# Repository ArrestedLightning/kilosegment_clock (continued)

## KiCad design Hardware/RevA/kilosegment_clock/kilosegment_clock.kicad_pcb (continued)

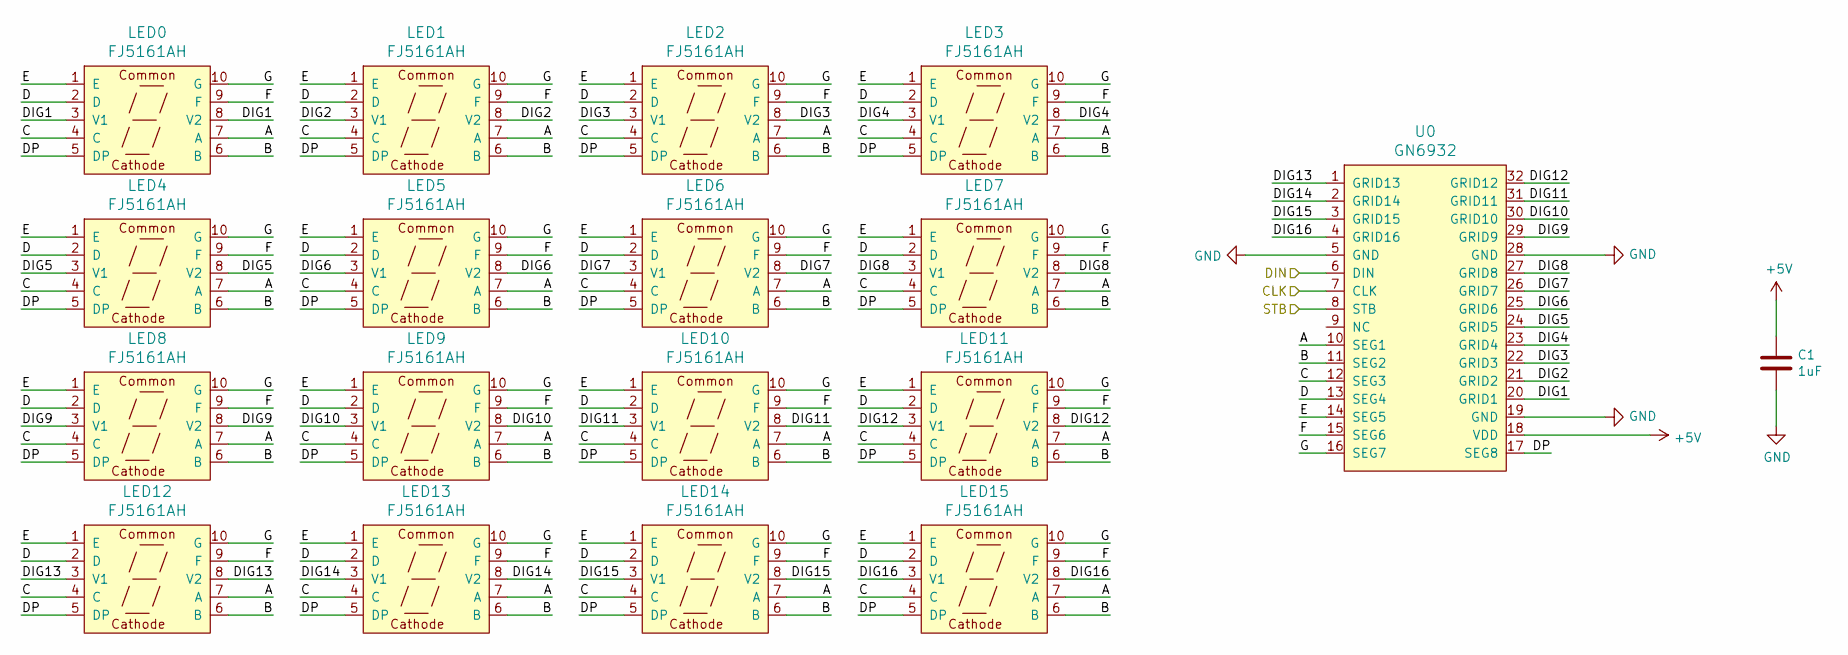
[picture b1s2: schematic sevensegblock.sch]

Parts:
C1: 1uF; C_0805_2012Metric_Pad1.18x1.45mm_HandSolder; Digikey 1276-1026-1-ND
LED0: FJ5161AH; LED-SEG-TH_FJ5161BH; LCSC Part C8092, C141367
LED1, LED2, LED3, LED4, LED5, LED6, LED7, LED8, LED9, LED10, LED11, LED12, LED13, LED14, LED15: FJ5161AH; LED-SEG-TH_FJ5161BH; LCSC Part C8092
U0: GN6932; SOP-32_L21.0-W7.5-P1.27-LS10.4-BL; LCSC Part C265476

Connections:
+5V: C1.1, U0.18 (VDD); also elsewhere on the board
/CLK: U0.7 (CLK); also elsewhere on the board
/CS0: U0.8 (STB); also elsewhere on the board
/DIN: U0.6 (DIN); also elsewhere on the board
/Sheet65B35949/A: LED0.7 (A), LED1.7 (A), LED2.7 (A), LED3.7 (A), LED4.7 (A), LED5.7 (A), LED6.7 (A), LED7.7 (A), LED8.7 (A), LED9.7 (A), LED10.7 (A), LED11.7 (A), LED12.7 (A), LED13.7 (A), LED14.7 (A), LED15.7 (A), U0.10 (SEG1)
/Sheet65B35949/B: LED0.6 (B), LED1.6 (B), LED2.6 (B), LED3.6 (B), LED4.6 (B), LED5.6 (B), LED6.6 (B), LED7.6 (B), LED8.6 (B), LED9.6 (B), LED10.6 (B), LED11.6 (B), LED12.6 (B), LED13.6 (B), LED14.6 (B), LED15.6 (B), U0.11 (SEG2)
/Sheet65B35949/C: LED0.4 (C), LED1.4 (C), LED2.4 (C), LED3.4 (C), LED4.4 (C), LED5.4 (C), LED6.4 (C), LED7.4 (C), LED8.4 (C), LED9.4 (C), LED10.4 (C), LED11.4 (C), LED12.4 (C), LED13.4 (C), LED14.4 (C), LED15.4 (C), U0.12 (SEG3)
/Sheet65B35949/D: LED0.2 (D), LED1.2 (D), LED2.2 (D), LED3.2 (D), LED4.2 (D), LED5.2 (D), LED6.2 (D), LED7.2 (D), LED8.2 (D), LED9.2 (D), LED10.2 (D), LED11.2 (D), LED12.2 (D), LED13.2 (D), LED14.2 (D), LED15.2 (D), U0.13 (SEG4)
/Sheet65B35949/DIG1: LED0.3 (V1), LED0.8 (V2), U0.20 (GRID1)
/Sheet65B35949/DIG2: LED1.3 (V1), LED1.8 (V2), U0.21 (GRID2)
/Sheet65B35949/DIG3: LED2.3 (V1), LED2.8 (V2), U0.22 (GRID3)
/Sheet65B35949/DIG4: LED3.3 (V1), LED3.8 (V2), U0.23 (GRID4)
/Sheet65B35949/DIG5: LED4.3 (V1), LED4.8 (V2), U0.24 (GRID5)
/Sheet65B35949/DIG6: LED5.3 (V1), LED5.8 (V2), U0.25 (GRID6)
/Sheet65B35949/DIG7: LED6.3 (V1), LED6.8 (V2), U0.26 (GRID7)
/Sheet65B35949/DIG8: LED7.3 (V1), LED7.8 (V2), U0.27 (GRID8)
/Sheet65B35949/DIG9: LED8.3 (V1), LED8.8 (V2), U0.29 (GRID9)
/Sheet65B35949/DIG10: LED9.3 (V1), LED9.8 (V2), U0.30 (GRID10)
/Sheet65B35949/DIG11: LED10.3 (V1), LED10.8 (V2), U0.31 (GRID11)
/Sheet65B35949/DIG12: LED11.3 (V1), LED11.8 (V2), U0.32 (GRID12)
/Sheet65B35949/DIG13: LED12.3 (V1), LED12.8 (V2), U0.1 (GRID13)
/Sheet65B35949/DIG14: LED13.3 (V1), LED13.8 (V2), U0.2 (GRID14)
/Sheet65B35949/DIG15: LED14.3 (V1), LED14.8 (V2), U0.3 (GRID15)
/Sheet65B35949/DIG16: LED15.3 (V1), LED15.8 (V2), U0.4 (GRID16)
/Sheet65B35949/DP: LED0.5 (DP), LED1.5 (DP), LED2.5 (DP), LED3.5 (DP), LED4.5 (DP), LED5.5 (DP), LED6.5 (DP), LED7.5 (DP), LED8.5 (DP), LED9.5 (DP), LED10.5 (DP), LED11.5 (DP), LED12.5 (DP), LED13.5 (DP), LED14.5 (DP), LED15.5 (DP), U0.17 (SEG8)
/Sheet65B35949/E: LED0.1 (E), LED1.1 (E), LED2.1 (E), LED3.1 (E), LED4.1 (E), LED5.1 (E), LED6.1 (E), LED7.1 (E), LED8.1 (E), LED9.1 (E), LED10.1 (E), LED11.1 (E), LED12.1 (E), LED13.1 (E), LED14.1 (E), LED15.1 (E), U0.14 (SEG5)
/Sheet65B35949/F: LED0.9 (F), LED1.9 (F), LED2.9 (F), LED3.9 (F), LED4.9 (F), LED5.9 (F), LED6.9 (F), LED7.9 (F), LED8.9 (F), LED9.9 (F), LED10.9 (F), LED11.9 (F), LED12.9 (F), LED13.9 (F), LED14.9 (F), LED15.9 (F), U0.15 (SEG6)
/Sheet65B35949/G: LED0.10 (G), LED1.10 (G), LED2.10 (G), LED3.10 (G), LED4.10 (G), LED5.10 (G), LED6.10 (G), LED7.10 (G), LED8.10 (G), LED9.10 (G), LED10.10 (G), LED11.10 (G), LED12.10 (G), LED13.10 (G), LED14.10 (G), LED15.10 (G), U0.16 (SEG7)
GND: C1.2, U0.5 (GND), U0.19 (GND), U0.28 (GND); also elsewhere on the board

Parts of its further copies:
C2, C3, C4, C5, C6, C7, C8, C9: 1uF; C_0805_2012Metric_Pad1.18x1.45mm_HandSolder; Digikey 1276-1026-1-ND
LED16, LED32, LED48, LED64, LED80, LED96, LED112, LED128: FJ5161AH; LED-SEG-TH_FJ5161BH; LCSC Part C8092, C141367
LED17, LED18, LED19, LED20, LED21, LED22, LED23, LED24, LED25, LED26, LED27, LED28, LED29, LED30, LED31, LED33, LED34, LED35, LED36, LED37, LED38, LED39, LED40, LED41, LED42, LED43, LED44, LED45, LED46, LED47, LED49, LED50, LED51, LED52, LED53, LED54, LED55, LED56, LED57, LED58, LED59, LED60, LED61, LED62, LED63, LED65, LED66, LED67, LED68, LED69, LED70, LED71, LED72, LED73, LED74, LED75, LED76, LED77, LED78, LED79, LED81, LED82, LED83, LED84, LED85, LED86, LED87, LED88, LED89, LED90, LED91, LED92, LED93, LED94, LED95, LED97, LED98, LED99, LED100, LED101, LED102, LED103, LED104, LED105, LED106, LED107, LED108, LED109, LED110, LED111, LED113, LED114, LED115, LED116, LED117, LED118, LED119, LED120, LED121, LED122, LED123, LED124, LED125, LED126, LED127, LED129, LED130, LED131, LED132, LED133, LED134, LED135, LED136, LED137, LED138, LED139, LED140, LED141, LED142, LED143: FJ5161AH; LED-SEG-TH_FJ5161BH; LCSC Part C8092
U1, U2, U3, U4, U5, U6, U7, U8: GN6932; SOP-32_L21.0-W7.5-P1.27-LS10.4-BL; LCSC Part C265476

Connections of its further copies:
+5V: C2.1, C3.1, C4.1, C5.1, C6.1, C7.1, C8.1, C9.1, U1.18 (VDD), U2.18 (VDD), U3.18 (VDD), U4.18 (VDD), U5.18 (VDD), U6.18 (VDD), U7.18 (VDD), U8.18 (VDD); also elsewhere on the board
/CLK: U1.7 (CLK), U2.7 (CLK), U3.7 (CLK), U4.7 (CLK), U5.7 (CLK), U6.7 (CLK), U7.7 (CLK), U8.7 (CLK); also elsewhere on the board
/CS1: U1.8 (STB); also elsewhere on the board
/CS2: U2.8 (STB); also elsewhere on the board
/CS3: U3.8 (STB); also elsewhere on the board
/CS4: U4.8 (STB); also elsewhere on the board
/CS5: U5.8 (STB); also elsewhere on the board
/CS6: U6.8 (STB); also elsewhere on the board
/CS7: U7.8 (STB); also elsewhere on the board
/CS8: U8.8 (STB); also elsewhere on the board
/DIN: U1.6 (DIN), U2.6 (DIN), U3.6 (DIN), U4.6 (DIN), U5.6 (DIN), U6.6 (DIN), U7.6 (DIN), U8.6 (DIN); also elsewhere on the board
/sheet65C5A503/A: LED16.7 (A), LED17.7 (A), LED18.7 (A), LED19.7 (A), LED20.7 (A), LED21.7 (A), LED22.7 (A), LED23.7 (A), LED24.7 (A), LED25.7 (A), LED26.7 (A), LED27.7 (A), LED28.7 (A), LED29.7 (A), LED30.7 (A), LED31.7 (A), U1.10 (SEG1)
/sheet65C5A503/B: LED16.6 (B), LED17.6 (B), LED18.6 (B), LED19.6 (B), LED20.6 (B), LED21.6 (B), LED22.6 (B), LED23.6 (B), LED24.6 (B), LED25.6 (B), LED26.6 (B), LED27.6 (B), LED28.6 (B), LED29.6 (B), LED30.6 (B), LED31.6 (B), U1.11 (SEG2)
/sheet65C5A503/C: LED16.4 (C), LED17.4 (C), LED18.4 (C), LED19.4 (C), LED20.4 (C), LED21.4 (C), LED22.4 (C), LED23.4 (C), LED24.4 (C), LED25.4 (C), LED26.4 (C), LED27.4 (C), LED28.4 (C), LED29.4 (C), LED30.4 (C), LED31.4 (C), U1.12 (SEG3)
/sheet65C5A503/D: LED16.2 (D), LED17.2 (D), LED18.2 (D), LED19.2 (D), LED20.2 (D), LED21.2 (D), LED22.2 (D), LED23.2 (D), LED24.2 (D), LED25.2 (D), LED26.2 (D), LED27.2 (D), LED28.2 (D), LED29.2 (D), LED30.2 (D), LED31.2 (D), U1.13 (SEG4)
/sheet65C5A503/DIG1: LED16.3 (V1), LED16.8 (V2), U1.20 (GRID1)
/sheet65C5A503/DIG2: LED17.3 (V1), LED17.8 (V2), U1.21 (GRID2)
/sheet65C5A503/DIG3: LED18.3 (V1), LED18.8 (V2), U1.22 (GRID3)
/sheet65C5A503/DIG4: LED19.3 (V1), LED19.8 (V2), U1.23 (GRID4)
/sheet65C5A503/DIG5: LED20.3 (V1), LED20.8 (V2), U1.24 (GRID5)
/sheet65C5A503/DIG6: LED21.3 (V1), LED21.8 (V2), U1.25 (GRID6)
/sheet65C5A503/DIG7: LED22.3 (V1), LED22.8 (V2), U1.26 (GRID7)
/sheet65C5A503/DIG8: LED23.3 (V1), LED23.8 (V2), U1.27 (GRID8)
/sheet65C5A503/DIG9: LED24.3 (V1), LED24.8 (V2), U1.29 (GRID9)
/sheet65C5A503/DIG10: LED25.3 (V1), LED25.8 (V2), U1.30 (GRID10)
/sheet65C5A503/DIG11: LED26.3 (V1), LED26.8 (V2), U1.31 (GRID11)
/sheet65C5A503/DIG12: LED27.3 (V1), LED27.8 (V2), U1.32 (GRID12)
/sheet65C5A503/DIG13: LED28.3 (V1), LED28.8 (V2), U1.1 (GRID13)
/sheet65C5A503/DIG14: LED29.3 (V1), LED29.8 (V2), U1.2 (GRID14)
/sheet65C5A503/DIG15: LED30.3 (V1), LED30.8 (V2), U1.3 (GRID15)
/sheet65C5A503/DIG16: LED31.3 (V1), LED31.8 (V2), U1.4 (GRID16)
/sheet65C5A503/DP: LED16.5 (DP), LED17.5 (DP), LED18.5 (DP), LED19.5 (DP), LED20.5 (DP), LED21.5 (DP), LED22.5 (DP), LED23.5 (DP), LED24.5 (DP), LED25.5 (DP), LED26.5 (DP), LED27.5 (DP), LED28.5 (DP), LED29.5 (DP), LED30.5 (DP), LED31.5 (DP), U1.17 (SEG8)
/sheet65C5A503/E: LED16.1 (E), LED17.1 (E), LED18.1 (E), LED19.1 (E), LED20.1 (E), LED21.1 (E), LED22.1 (E), LED23.1 (E), LED24.1 (E), LED25.1 (E), LED26.1 (E), LED27.1 (E), LED28.1 (E), LED29.1 (E), LED30.1 (E), LED31.1 (E), U1.14 (SEG5)
/sheet65C5A503/F: LED16.9 (F), LED17.9 (F), LED18.9 (F), LED19.9 (F), LED20.9 (F), LED21.9 (F), LED22.9 (F), LED23.9 (F), LED24.9 (F), LED25.9 (F), LED26.9 (F), LED27.9 (F), LED28.9 (F), LED29.9 (F), LED30.9 (F), LED31.9 (F), U1.15 (SEG6)
/sheet65C5A503/G: LED16.10 (G), LED17.10 (G), LED18.10 (G), LED19.10 (G), LED20.10 (G), LED21.10 (G), LED22.10 (G), LED23.10 (G), LED24.10 (G), LED25.10 (G), LED26.10 (G), LED27.10 (G), LED28.10 (G), LED29.10 (G), LED30.10 (G), LED31.10 (G), U1.16 (SEG7)
/sheet65E7B3E1/A: LED128.7 (A), LED129.7 (A), LED130.7 (A), LED131.7 (A), LED132.7 (A), LED133.7 (A), LED134.7 (A), LED135.7 (A), LED136.7 (A), LED137.7 (A), LED138.7 (A), LED139.7 (A), LED140.7 (A), LED141.7 (A), LED142.7 (A), LED143.7 (A), U8.10 (SEG1)
/sheet65E7B3E1/B: LED128.6 (B), LED129.6 (B), LED130.6 (B), LED131.6 (B), LED132.6 (B), LED133.6 (B), LED134.6 (B), LED135.6 (B), LED136.6 (B), LED137.6 (B), LED138.6 (B), LED139.6 (B), LED140.6 (B), LED141.6 (B), LED142.6 (B), LED143.6 (B), U8.11 (SEG2)
/sheet65E7B3E1/C: LED128.4 (C), LED129.4 (C), LED130.4 (C), LED131.4 (C), LED132.4 (C), LED133.4 (C), LED134.4 (C), LED135.4 (C), LED136.4 (C), LED137.4 (C), LED138.4 (C), LED139.4 (C), LED140.4 (C), LED141.4 (C), LED142.4 (C), LED143.4 (C), U8.12 (SEG3)
/sheet65E7B3E1/D: LED128.2 (D), LED129.2 (D), LED130.2 (D), LED131.2 (D), LED132.2 (D), LED133.2 (D), LED134.2 (D), LED135.2 (D), LED136.2 (D), LED137.2 (D), LED138.2 (D), LED139.2 (D), LED140.2 (D), LED141.2 (D), LED142.2 (D), LED143.2 (D), U8.13 (SEG4)
/sheet65E7B3E1/DIG1: LED128.3 (V1), LED128.8 (V2), U8.20 (GRID1)
/sheet65E7B3E1/DIG2: LED129.3 (V1), LED129.8 (V2), U8.21 (GRID2)
/sheet65E7B3E1/DIG3: LED130.3 (V1), LED130.8 (V2), U8.22 (GRID3)
/sheet65E7B3E1/DIG4: LED131.3 (V1), LED131.8 (V2), U8.23 (GRID4)
/sheet65E7B3E1/DIG5: LED132.3 (V1), LED132.8 (V2), U8.24 (GRID5)
/sheet65E7B3E1/DIG6: LED133.3 (V1), LED133.8 (V2), U8.25 (GRID6)
/sheet65E7B3E1/DIG7: LED134.3 (V1), LED134.8 (V2), U8.26 (GRID7)
/sheet65E7B3E1/DIG8: LED135.3 (V1), LED135.8 (V2), U8.27 (GRID8)
/sheet65E7B3E1/DIG9: LED136.3 (V1), LED136.8 (V2), U8.29 (GRID9)
/sheet65E7B3E1/DIG10: LED137.3 (V1), LED137.8 (V2), U8.30 (GRID10)
/sheet65E7B3E1/DIG11: LED138.3 (V1), LED138.8 (V2), U8.31 (GRID11)
/sheet65E7B3E1/DIG12: LED139.3 (V1), LED139.8 (V2), U8.32 (GRID12)
/sheet65E7B3E1/DIG13: LED140.3 (V1), LED140.8 (V2), U8.1 (GRID13)
/sheet65E7B3E1/DIG14: LED141.3 (V1), LED141.8 (V2), U8.2 (GRID14)
/sheet65E7B3E1/DIG15: LED142.3 (V1), LED142.8 (V2), U8.3 (GRID15)
/sheet65E7B3E1/DIG16: LED143.3 (V1), LED143.8 (V2), U8.4 (GRID16)
/sheet65E7B3E1/DP: LED128.5 (DP), LED129.5 (DP), LED130.5 (DP), LED131.5 (DP), LED132.5 (DP), LED133.5 (DP), LED134.5 (DP), LED135.5 (DP), LED136.5 (DP), LED137.5 (DP), LED138.5 (DP), LED139.5 (DP), LED140.5 (DP), LED141.5 (DP), LED142.5 (DP), LED143.5 (DP), U8.17 (SEG8)
/sheet65E7B3E1/E: LED128.1 (E), LED129.1 (E), LED130.1 (E), LED131.1 (E), LED132.1 (E), LED133.1 (E), LED134.1 (E), LED135.1 (E), LED136.1 (E), LED137.1 (E), LED138.1 (E), LED139.1 (E), LED140.1 (E), LED141.1 (E), LED142.1 (E), LED143.1 (E), U8.14 (SEG5)
/sheet65E7B3E1/F: LED128.9 (F), LED129.9 (F), LED130.9 (F), LED131.9 (F), LED132.9 (F), LED133.9 (F), LED134.9 (F), LED135.9 (F), LED136.9 (F), LED137.9 (F), LED138.9 (F), LED139.9 (F), LED140.9 (F), LED141.9 (F), LED142.9 (F), LED143.9 (F), U8.15 (SEG6)
/sheet65E7B3E1/G: LED128.10 (G), LED129.10 (G), LED130.10 (G), LED131.10 (G), LED132.10 (G), LED133.10 (G), LED134.10 (G), LED135.10 (G), LED136.10 (G), LED137.10 (G), LED138.10 (G), LED139.10 (G), LED140.10 (G), LED141.10 (G), LED142.10 (G), LED143.10 (G), U8.16 (SEG7)
/sheet65E77CCE/A: LED48.7 (A), LED49.7 (A), LED50.7 (A), LED51.7 (A), LED52.7 (A), LED53.7 (A), LED54.7 (A), LED55.7 (A), LED56.7 (A), LED57.7 (A), LED58.7 (A), LED59.7 (A), LED60.7 (A), LED61.7 (A), LED62.7 (A), LED63.7 (A), U3.10 (SEG1)
/sheet65E77CCE/B: LED48.6 (B), LED49.6 (B), LED50.6 (B), LED51.6 (B), LED52.6 (B), LED53.6 (B), LED54.6 (B), LED55.6 (B), LED56.6 (B), LED57.6 (B), LED58.6 (B), LED59.6 (B), LED60.6 (B), LED61.6 (B), LED62.6 (B), LED63.6 (B), U3.11 (SEG2)
/sheet65E77CCE/C: LED48.4 (C), LED49.4 (C), LED50.4 (C), LED51.4 (C), LED52.4 (C), LED53.4 (C), LED54.4 (C), LED55.4 (C), LED56.4 (C), LED57.4 (C), LED58.4 (C), LED59.4 (C), LED60.4 (C), LED61.4 (C), LED62.4 (C), LED63.4 (C), U3.12 (SEG3)
/sheet65E77CCE/D: LED48.2 (D), LED49.2 (D), LED50.2 (D), LED51.2 (D), LED52.2 (D), LED53.2 (D), LED54.2 (D), LED55.2 (D), LED56.2 (D), LED57.2 (D), LED58.2 (D), LED59.2 (D), LED60.2 (D), LED61.2 (D), LED62.2 (D), LED63.2 (D), U3.13 (SEG4)
/sheet65E77CCE/DIG1: LED48.3 (V1), LED48.8 (V2), U3.20 (GRID1)
/sheet65E77CCE/DIG2: LED49.3 (V1), LED49.8 (V2), U3.21 (GRID2)
/sheet65E77CCE/DIG3: LED50.3 (V1), LED50.8 (V2), U3.22 (GRID3)
/sheet65E77CCE/DIG4: LED51.3 (V1), LED51.8 (V2), U3.23 (GRID4)
/sheet65E77CCE/DIG5: LED52.3 (V1), LED52.8 (V2), U3.24 (GRID5)
/sheet65E77CCE/DIG6: LED53.3 (V1), LED53.8 (V2), U3.25 (GRID6)
/sheet65E77CCE/DIG7: LED54.3 (V1), LED54.8 (V2), U3.26 (GRID7)
/sheet65E77CCE/DIG8: LED55.3 (V1), LED55.8 (V2), U3.27 (GRID8)
/sheet65E77CCE/DIG9: LED56.3 (V1), LED56.8 (V2), U3.29 (GRID9)
/sheet65E77CCE/DIG10: LED57.3 (V1), LED57.8 (V2), U3.30 (GRID10)
/sheet65E77CCE/DIG11: LED58.3 (V1), LED58.8 (V2), U3.31 (GRID11)
/sheet65E77CCE/DIG12: LED59.3 (V1), LED59.8 (V2), U3.32 (GRID12)
/sheet65E77CCE/DIG13: LED60.3 (V1), LED60.8 (V2), U3.1 (GRID13)
/sheet65E77CCE/DIG14: LED61.3 (V1), LED61.8 (V2), U3.2 (GRID14)
/sheet65E77CCE/DIG15: LED62.3 (V1), LED62.8 (V2), U3.3 (GRID15)
/sheet65E77CCE/DIG16: LED63.3 (V1), LED63.8 (V2), U3.4 (GRID16)
/sheet65E77CCE/DP: LED48.5 (DP), LED49.5 (DP), LED50.5 (DP), LED51.5 (DP), LED52.5 (DP), LED53.5 (DP), LED54.5 (DP), LED55.5 (DP), LED56.5 (DP), LED57.5 (DP), LED58.5 (DP), LED59.5 (DP), LED60.5 (DP), LED61.5 (DP), LED62.5 (DP), LED63.5 (DP), U3.17 (SEG8)
/sheet65E77CCE/E: LED48.1 (E), LED49.1 (E), LED50.1 (E), LED51.1 (E), LED52.1 (E), LED53.1 (E), LED54.1 (E), LED55.1 (E), LED56.1 (E), LED57.1 (E), LED58.1 (E), LED59.1 (E), LED60.1 (E), LED61.1 (E), LED62.1 (E), LED63.1 (E), U3.14 (SEG5)
/sheet65E77CCE/F: LED48.9 (F), LED49.9 (F), LED50.9 (F), LED51.9 (F), LED52.9 (F), LED53.9 (F), LED54.9 (F), LED55.9 (F), LED56.9 (F), LED57.9 (F), LED58.9 (F), LED59.9 (F), LED60.9 (F), LED61.9 (F), LED62.9 (F), LED63.9 (F), U3.15 (SEG6)
/sheet65E77CCE/G: LED48.10 (G), LED49.10 (G), LED50.10 (G), LED51.10 (G), LED52.10 (G), LED53.10 (G), LED54.10 (G), LED55.10 (G), LED56.10 (G), LED57.10 (G), LED58.10 (G), LED59.10 (G), LED60.10 (G), LED61.10 (G), LED62.10 (G), LED63.10 (G), U3.16 (SEG7)
/sheet65E79B9E/A: LED64.7 (A), LED65.7 (A), LED66.7 (A), LED67.7 (A), LED68.7 (A), LED69.7 (A), LED70.7 (A), LED71.7 (A), LED72.7 (A), LED73.7 (A), LED74.7 (A), LED75.7 (A), LED76.7 (A), LED77.7 (A), LED78.7 (A), LED79.7 (A), U4.10 (SEG1)
/sheet65E79B9E/B: LED64.6 (B), LED65.6 (B), LED66.6 (B), LED67.6 (B), LED68.6 (B), LED69.6 (B), LED70.6 (B), LED71.6 (B), LED72.6 (B), LED73.6 (B), LED74.6 (B), LED75.6 (B), LED76.6 (B), LED77.6 (B), LED78.6 (B), LED79.6 (B), U4.11 (SEG2)
/sheet65E79B9E/C: LED64.4 (C), LED65.4 (C), LED66.4 (C), LED67.4 (C), LED68.4 (C), LED69.4 (C), LED70.4 (C), LED71.4 (C), LED72.4 (C), LED73.4 (C), LED74.4 (C), LED75.4 (C), LED76.4 (C), LED77.4 (C), LED78.4 (C), LED79.4 (C), U4.12 (SEG3)
/sheet65E79B9E/D: LED64.2 (D), LED65.2 (D), LED66.2 (D), LED67.2 (D), LED68.2 (D), LED69.2 (D), LED70.2 (D), LED71.2 (D), LED72.2 (D), LED73.2 (D), LED74.2 (D), LED75.2 (D), LED76.2 (D), LED77.2 (D), LED78.2 (D), LED79.2 (D), U4.13 (SEG4)
/sheet65E79B9E/DIG1: LED64.3 (V1), LED64.8 (V2), U4.20 (GRID1)
/sheet65E79B9E/DIG2: LED65.3 (V1), LED65.8 (V2), U4.21 (GRID2)
/sheet65E79B9E/DIG3: LED66.3 (V1), LED66.8 (V2), U4.22 (GRID3)
/sheet65E79B9E/DIG4: LED67.3 (V1), LED67.8 (V2), U4.23 (GRID4)
/sheet65E79B9E/DIG5: LED68.3 (V1), LED68.8 (V2), U4.24 (GRID5)
/sheet65E79B9E/DIG6: LED69.3 (V1), LED69.8 (V2), U4.25 (GRID6)
/sheet65E79B9E/DIG7: LED70.3 (V1), LED70.8 (V2), U4.26 (GRID7)
/sheet65E79B9E/DIG8: LED71.3 (V1), LED71.8 (V2), U4.27 (GRID8)
/sheet65E79B9E/DIG9: LED72.3 (V1), LED72.8 (V2), U4.29 (GRID9)
/sheet65E79B9E/DIG10: LED73.3 (V1), LED73.8 (V2), U4.30 (GRID10)
/sheet65E79B9E/DIG11: LED74.3 (V1), LED74.8 (V2), U4.31 (GRID11)
/sheet65E79B9E/DIG12: LED75.3 (V1), LED75.8 (V2), U4.32 (GRID12)
/sheet65E79B9E/DIG13: LED76.3 (V1), LED76.8 (V2), U4.1 (GRID13)
/sheet65E79B9E/DIG14: LED77.3 (V1), LED77.8 (V2), U4.2 (GRID14)
/sheet65E79B9E/DIG15: LED78.3 (V1), LED78.8 (V2), U4.3 (GRID15)
/sheet65E79B9E/DIG16: LED79.3 (V1), LED79.8 (V2), U4.4 (GRID16)
/sheet65E79B9E/DP: LED64.5 (DP), LED65.5 (DP), LED66.5 (DP), LED67.5 (DP), LED68.5 (DP), LED69.5 (DP), LED70.5 (DP), LED71.5 (DP), LED72.5 (DP), LED73.5 (DP), LED74.5 (DP), LED75.5 (DP), LED76.5 (DP), LED77.5 (DP), LED78.5 (DP), LED79.5 (DP), U4.17 (SEG8)
/sheet65E79B9E/E: LED64.1 (E), LED65.1 (E), LED66.1 (E), LED67.1 (E), LED68.1 (E), LED69.1 (E), LED70.1 (E), LED71.1 (E), LED72.1 (E), LED73.1 (E), LED74.1 (E), LED75.1 (E), LED76.1 (E), LED77.1 (E), LED78.1 (E), LED79.1 (E), U4.14 (SEG5)
/sheet65E79B9E/F: LED64.9 (F), LED65.9 (F), LED66.9 (F), LED67.9 (F), LED68.9 (F), LED69.9 (F), LED70.9 (F), LED71.9 (F), LED72.9 (F), LED73.9 (F), LED74.9 (F), LED75.9 (F), LED76.9 (F), LED77.9 (F), LED78.9 (F), LED79.9 (F), U4.15 (SEG6)
/sheet65E79B9E/G: LED64.10 (G), LED65.10 (G), LED66.10 (G), LED67.10 (G), LED68.10 (G), LED69.10 (G), LED70.10 (G), LED71.10 (G), LED72.10 (G), LED73.10 (G), LED74.10 (G), LED75.10 (G), LED76.10 (G), LED77.10 (G), LED78.10 (G), LED79.10 (G), U4.16 (SEG7)
/sheet65E79BA3/A: LED80.7 (A), LED81.7 (A), LED82.7 (A), LED83.7 (A), LED84.7 (A), LED85.7 (A), LED86.7 (A), LED87.7 (A), LED88.7 (A), LED89.7 (A), LED90.7 (A), LED91.7 (A), LED92.7 (A), LED93.7 (A), LED94.7 (A), LED95.7 (A), U5.10 (SEG1)
/sheet65E79BA3/B: LED80.6 (B), LED81.6 (B), LED82.6 (B), LED83.6 (B), LED84.6 (B), LED85.6 (B), LED86.6 (B), LED87.6 (B), LED88.6 (B), LED89.6 (B), LED90.6 (B), LED91.6 (B), LED92.6 (B), LED93.6 (B), LED94.6 (B), LED95.6 (B), U5.11 (SEG2)
/sheet65E79BA3/C: LED80.4 (C), LED81.4 (C), LED82.4 (C), LED83.4 (C), LED84.4 (C), LED85.4 (C), LED86.4 (C), LED87.4 (C), LED88.4 (C), LED89.4 (C), LED90.4 (C), LED91.4 (C), LED92.4 (C), LED93.4 (C), LED94.4 (C), LED95.4 (C), U5.12 (SEG3)
/sheet65E79BA3/D: LED80.2 (D), LED81.2 (D), LED82.2 (D), LED83.2 (D), LED84.2 (D), LED85.2 (D), LED86.2 (D), LED87.2 (D), LED88.2 (D), LED89.2 (D), LED90.2 (D), LED91.2 (D), LED92.2 (D), LED93.2 (D), LED94.2 (D), LED95.2 (D), U5.13 (SEG4)
/sheet65E79BA3/DIG1: LED80.3 (V1), LED80.8 (V2), U5.20 (GRID1)
/sheet65E79BA3/DIG2: LED81.3 (V1), LED81.8 (V2), U5.21 (GRID2)
/sheet65E79BA3/DIG3: LED82.3 (V1), LED82.8 (V2), U5.22 (GRID3)
/sheet65E79BA3/DIG4: LED83.3 (V1), LED83.8 (V2), U5.23 (GRID4)
/sheet65E79BA3/DIG5: LED84.3 (V1), LED84.8 (V2), U5.24 (GRID5)
/sheet65E79BA3/DIG6: LED85.3 (V1), LED85.8 (V2), U5.25 (GRID6)
/sheet65E79BA3/DIG7: LED86.3 (V1), LED86.8 (V2), U5.26 (GRID7)
/sheet65E79BA3/DIG8: LED87.3 (V1), LED87.8 (V2), U5.27 (GRID8)
/sheet65E79BA3/DIG9: LED88.3 (V1), LED88.8 (V2), U5.29 (GRID9)
/sheet65E79BA3/DIG10: LED89.3 (V1), LED89.8 (V2), U5.30 (GRID10)
/sheet65E79BA3/DIG11: LED90.3 (V1), LED90.8 (V2), U5.31 (GRID11)
/sheet65E79BA3/DIG12: LED91.3 (V1), LED91.8 (V2), U5.32 (GRID12)
/sheet65E79BA3/DIG13: LED92.3 (V1), LED92.8 (V2), U5.1 (GRID13)
/sheet65E79BA3/DIG14: LED93.3 (V1), LED93.8 (V2), U5.2 (GRID14)
/sheet65E79BA3/DIG15: LED94.3 (V1), LED94.8 (V2), U5.3 (GRID15)
/sheet65E79BA3/DIG16: LED95.3 (V1), LED95.8 (V2), U5.4 (GRID16)
/sheet65E79BA3/DP: LED80.5 (DP), LED81.5 (DP), LED82.5 (DP), LED83.5 (DP), LED84.5 (DP), LED85.5 (DP), LED86.5 (DP), LED87.5 (DP), LED88.5 (DP), LED89.5 (DP), LED90.5 (DP), LED91.5 (DP), LED92.5 (DP), LED93.5 (DP), LED94.5 (DP), LED95.5 (DP), U5.17 (SEG8)
/sheet65E79BA3/E: LED80.1 (E), LED81.1 (E), LED82.1 (E), LED83.1 (E), LED84.1 (E), LED85.1 (E), LED86.1 (E), LED87.1 (E), LED88.1 (E), LED89.1 (E), LED90.1 (E), LED91.1 (E), LED92.1 (E), LED93.1 (E), LED94.1 (E), LED95.1 (E), U5.14 (SEG5)
/sheet65E79BA3/F: LED80.9 (F), LED81.9 (F), LED82.9 (F), LED83.9 (F), LED84.9 (F), LED85.9 (F), LED86.9 (F), LED87.9 (F), LED88.9 (F), LED89.9 (F), LED90.9 (F), LED91.9 (F), LED92.9 (F), LED93.9 (F), LED94.9 (F), LED95.9 (F), U5.15 (SEG6)
/sheet65E79BA3/G: LED80.10 (G), LED81.10 (G), LED82.10 (G), LED83.10 (G), LED84.10 (G), LED85.10 (G), LED86.10 (G), LED87.10 (G), LED88.10 (G), LED89.10 (G), LED90.10 (G), LED91.10 (G), LED92.10 (G), LED93.10 (G), LED94.10 (G), LED95.10 (G), U5.16 (SEG7)
/sheet65E79BB2/A: LED96.7 (A), LED97.7 (A), LED98.7 (A), LED99.7 (A), LED100.7 (A), LED101.7 (A), LED102.7 (A), LED103.7 (A), LED104.7 (A), LED105.7 (A), LED106.7 (A), LED107.7 (A), LED108.7 (A), LED109.7 (A), LED110.7 (A), LED111.7 (A), U6.10 (SEG1)
/sheet65E79BB2/B: LED96.6 (B), LED97.6 (B), LED98.6 (B), LED99.6 (B), LED100.6 (B), LED101.6 (B), LED102.6 (B), LED103.6 (B), LED104.6 (B), LED105.6 (B), LED106.6 (B), LED107.6 (B), LED108.6 (B), LED109.6 (B), LED110.6 (B), LED111.6 (B), U6.11 (SEG2)
/sheet65E79BB2/C: LED96.4 (C), LED97.4 (C), LED98.4 (C), LED99.4 (C), LED100.4 (C), LED101.4 (C), LED102.4 (C), LED103.4 (C), LED104.4 (C), LED105.4 (C), LED106.4 (C), LED107.4 (C), LED108.4 (C), LED109.4 (C), LED110.4 (C), LED111.4 (C), U6.12 (SEG3)
/sheet65E79BB2/D: LED96.2 (D), LED97.2 (D), LED98.2 (D), LED99.2 (D), LED100.2 (D), LED101.2 (D), LED102.2 (D), LED103.2 (D), LED104.2 (D), LED105.2 (D), LED106.2 (D), LED107.2 (D), LED108.2 (D), LED109.2 (D), LED110.2 (D), LED111.2 (D), U6.13 (SEG4)
/sheet65E79BB2/DIG1: LED96.3 (V1), LED96.8 (V2), U6.20 (GRID1)
/sheet65E79BB2/DIG2: LED97.3 (V1), LED97.8 (V2), U6.21 (GRID2)
/sheet65E79BB2/DIG3: LED98.3 (V1), LED98.8 (V2), U6.22 (GRID3)
/sheet65E79BB2/DIG4: LED99.3 (V1), LED99.8 (V2), U6.23 (GRID4)
/sheet65E79BB2/DIG5: LED100.3 (V1), LED100.8 (V2), U6.24 (GRID5)
/sheet65E79BB2/DIG6: LED101.3 (V1), LED101.8 (V2), U6.25 (GRID6)
/sheet65E79BB2/DIG7: LED102.3 (V1), LED102.8 (V2), U6.26 (GRID7)
/sheet65E79BB2/DIG8: LED103.3 (V1), LED103.8 (V2), U6.27 (GRID8)
/sheet65E79BB2/DIG9: LED104.3 (V1), LED104.8 (V2), U6.29 (GRID9)
/sheet65E79BB2/DIG10: LED105.3 (V1), LED105.8 (V2), U6.30 (GRID10)
/sheet65E79BB2/DIG11: LED106.3 (V1), LED106.8 (V2), U6.31 (GRID11)
/sheet65E79BB2/DIG12: LED107.3 (V1), LED107.8 (V2), U6.32 (GRID12)
/sheet65E79BB2/DIG13: LED108.3 (V1), LED108.8 (V2), U6.1 (GRID13)
/sheet65E79BB2/DIG14: LED109.3 (V1), LED109.8 (V2), U6.2 (GRID14)
/sheet65E79BB2/DIG15: LED110.3 (V1), LED110.8 (V2), U6.3 (GRID15)
/sheet65E79BB2/DIG16: LED111.3 (V1), LED111.8 (V2), U6.4 (GRID16)
/sheet65E79BB2/DP: LED96.5 (DP), LED97.5 (DP), LED98.5 (DP), LED99.5 (DP), LED100.5 (DP), LED101.5 (DP), LED102.5 (DP), LED103.5 (DP), LED104.5 (DP), LED105.5 (DP), LED106.5 (DP), LED107.5 (DP), LED108.5 (DP), LED109.5 (DP), LED110.5 (DP), LED111.5 (DP), U6.17 (SEG8)
/sheet65E79BB2/E: LED96.1 (E), LED97.1 (E), LED98.1 (E), LED99.1 (E), LED100.1 (E), LED101.1 (E), LED102.1 (E), LED103.1 (E), LED104.1 (E), LED105.1 (E), LED106.1 (E), LED107.1 (E), LED108.1 (E), LED109.1 (E), LED110.1 (E), LED111.1 (E), U6.14 (SEG5)
/sheet65E79BB2/F: LED96.9 (F), LED97.9 (F), LED98.9 (F), LED99.9 (F), LED100.9 (F), LED101.9 (F), LED102.9 (F), LED103.9 (F), LED104.9 (F), LED105.9 (F), LED106.9 (F), LED107.9 (F), LED108.9 (F), LED109.9 (F), LED110.9 (F), LED111.9 (F), U6.15 (SEG6)
/sheet65E79BB2/G: LED96.10 (G), LED97.10 (G), LED98.10 (G), LED99.10 (G), LED100.10 (G), LED101.10 (G), LED102.10 (G), LED103.10 (G), LED104.10 (G), LED105.10 (G), LED106.10 (G), LED107.10 (G), LED108.10 (G), LED109.10 (G), LED110.10 (G), LED111.10 (G), U6.16 (SEG7)
/sheet65E79BBC/A: LED112.7 (A), LED113.7 (A), LED114.7 (A), LED115.7 (A), LED116.7 (A), LED117.7 (A), LED118.7 (A), LED119.7 (A), LED120.7 (A), LED121.7 (A), LED122.7 (A), LED123.7 (A), LED124.7 (A), LED125.7 (A), LED126.7 (A), LED127.7 (A), U7.10 (SEG1)
/sheet65E79BBC/B: LED112.6 (B), LED113.6 (B), LED114.6 (B), LED115.6 (B), LED116.6 (B), LED117.6 (B), LED118.6 (B), LED119.6 (B), LED120.6 (B), LED121.6 (B), LED122.6 (B), LED123.6 (B), LED124.6 (B), LED125.6 (B), LED126.6 (B), LED127.6 (B), U7.11 (SEG2)
/sheet65E79BBC/C: LED112.4 (C), LED113.4 (C), LED114.4 (C), LED115.4 (C), LED116.4 (C), LED117.4 (C), LED118.4 (C), LED119.4 (C), LED120.4 (C), LED121.4 (C), LED122.4 (C), LED123.4 (C), LED124.4 (C), LED125.4 (C), LED126.4 (C), LED127.4 (C), U7.12 (SEG3)
/sheet65E79BBC/D: LED112.2 (D), LED113.2 (D), LED114.2 (D), LED115.2 (D), LED116.2 (D), LED117.2 (D), LED118.2 (D), LED119.2 (D), LED120.2 (D), LED121.2 (D), LED122.2 (D), LED123.2 (D), LED124.2 (D), LED125.2 (D), LED126.2 (D), LED127.2 (D), U7.13 (SEG4)
/sheet65E79BBC/DIG1: LED112.3 (V1), LED112.8 (V2), U7.20 (GRID1)
/sheet65E79BBC/DIG2: LED113.3 (V1), LED113.8 (V2), U7.21 (GRID2)
/sheet65E79BBC/DIG3: LED114.3 (V1), LED114.8 (V2), U7.22 (GRID3)
/sheet65E79BBC/DIG4: LED115.3 (V1), LED115.8 (V2), U7.23 (GRID4)
/sheet65E79BBC/DIG5: LED116.3 (V1), LED116.8 (V2), U7.24 (GRID5)
/sheet65E79BBC/DIG6: LED117.3 (V1), LED117.8 (V2), U7.25 (GRID6)
/sheet65E79BBC/DIG7: LED118.3 (V1), LED118.8 (V2), U7.26 (GRID7)
/sheet65E79BBC/DIG8: LED119.3 (V1), LED119.8 (V2), U7.27 (GRID8)
/sheet65E79BBC/DIG9: LED120.3 (V1), LED120.8 (V2), U7.29 (GRID9)
/sheet65E79BBC/DIG10: LED121.3 (V1), LED121.8 (V2), U7.30 (GRID10)
/sheet65E79BBC/DIG11: LED122.3 (V1), LED122.8 (V2), U7.31 (GRID11)
/sheet65E79BBC/DIG12: LED123.3 (V1), LED123.8 (V2), U7.32 (GRID12)
/sheet65E79BBC/DIG13: LED124.3 (V1), LED124.8 (V2), U7.1 (GRID13)
/sheet65E79BBC/DIG14: LED125.3 (V1), LED125.8 (V2), U7.2 (GRID14)
/sheet65E79BBC/DIG15: LED126.3 (V1), LED126.8 (V2), U7.3 (GRID15)
/sheet65E79BBC/DIG16: LED127.3 (V1), LED127.8 (V2), U7.4 (GRID16)
/sheet65E79BBC/DP: LED112.5 (DP), LED113.5 (DP), LED114.5 (DP), LED115.5 (DP), LED116.5 (DP), LED117.5 (DP), LED118.5 (DP), LED119.5 (DP), LED120.5 (DP), LED121.5 (DP), LED122.5 (DP), LED123.5 (DP), LED124.5 (DP), LED125.5 (DP), LED126.5 (DP), LED127.5 (DP), U7.17 (SEG8)
/sheet65E79BBC/E: LED112.1 (E), LED113.1 (E), LED114.1 (E), LED115.1 (E), LED116.1 (E), LED117.1 (E), LED118.1 (E), LED119.1 (E), LED120.1 (E), LED121.1 (E), LED122.1 (E), LED123.1 (E), LED124.1 (E), LED125.1 (E), LED126.1 (E), LED127.1 (E), U7.14 (SEG5)
/sheet65E79BBC/F: LED112.9 (F), LED113.9 (F), LED114.9 (F), LED115.9 (F), LED116.9 (F), LED117.9 (F), LED118.9 (F), LED119.9 (F), LED120.9 (F), LED121.9 (F), LED122.9 (F), LED123.9 (F), LED124.9 (F), LED125.9 (F), LED126.9 (F), LED127.9 (F), U7.15 (SEG6)
/sheet65E79BBC/G: LED112.10 (G), LED113.10 (G), LED114.10 (G), LED115.10 (G), LED116.10 (G), LED117.10 (G), LED118.10 (G), LED119.10 (G), LED120.10 (G), LED121.10 (G), LED122.10 (G), LED123.10 (G), LED124.10 (G), LED125.10 (G), LED126.10 (G), LED127.10 (G), U7.16 (SEG7)
/sheet65E77961/A: LED32.7 (A), LED33.7 (A), LED34.7 (A), LED35.7 (A), LED36.7 (A), LED37.7 (A), LED38.7 (A), LED39.7 (A), LED40.7 (A), LED41.7 (A), LED42.7 (A), LED43.7 (A), LED44.7 (A), LED45.7 (A), LED46.7 (A), LED47.7 (A), U2.10 (SEG1)
/sheet65E77961/B: LED32.6 (B), LED33.6 (B), LED34.6 (B), LED35.6 (B), LED36.6 (B), LED37.6 (B), LED38.6 (B), LED39.6 (B), LED40.6 (B), LED41.6 (B), LED42.6 (B), LED43.6 (B), LED44.6 (B), LED45.6 (B), LED46.6 (B), LED47.6 (B), U2.11 (SEG2)
/sheet65E77961/C: LED32.4 (C), LED33.4 (C), LED34.4 (C), LED35.4 (C), LED36.4 (C), LED37.4 (C), LED38.4 (C), LED39.4 (C), LED40.4 (C), LED41.4 (C), LED42.4 (C), LED43.4 (C), LED44.4 (C), LED45.4 (C), LED46.4 (C), LED47.4 (C), U2.12 (SEG3)
/sheet65E77961/D: LED32.2 (D), LED33.2 (D), LED34.2 (D), LED35.2 (D), LED36.2 (D), LED37.2 (D), LED38.2 (D), LED39.2 (D), LED40.2 (D), LED41.2 (D), LED42.2 (D), LED43.2 (D), LED44.2 (D), LED45.2 (D), LED46.2 (D), LED47.2 (D), U2.13 (SEG4)
/sheet65E77961/DIG1: LED32.3 (V1), LED32.8 (V2), U2.20 (GRID1)
/sheet65E77961/DIG2: LED33.3 (V1), LED33.8 (V2), U2.21 (GRID2)
/sheet65E77961/DIG3: LED34.3 (V1), LED34.8 (V2), U2.22 (GRID3)
/sheet65E77961/DIG4: LED35.3 (V1), LED35.8 (V2), U2.23 (GRID4)
/sheet65E77961/DIG5: LED36.3 (V1), LED36.8 (V2), U2.24 (GRID5)
/sheet65E77961/DIG6: LED37.3 (V1), LED37.8 (V2), U2.25 (GRID6)
/sheet65E77961/DIG7: LED38.3 (V1), LED38.8 (V2), U2.26 (GRID7)
/sheet65E77961/DIG8: LED39.3 (V1), LED39.8 (V2), U2.27 (GRID8)
/sheet65E77961/DIG9: LED40.3 (V1), LED40.8 (V2), U2.29 (GRID9)
/sheet65E77961/DIG10: LED41.3 (V1), LED41.8 (V2), U2.30 (GRID10)
/sheet65E77961/DIG11: LED42.3 (V1), LED42.8 (V2), U2.31 (GRID11)
/sheet65E77961/DIG12: LED43.3 (V1), LED43.8 (V2), U2.32 (GRID12)
/sheet65E77961/DIG13: LED44.3 (V1), LED44.8 (V2), U2.1 (GRID13)
/sheet65E77961/DIG14: LED45.3 (V1), LED45.8 (V2), U2.2 (GRID14)
/sheet65E77961/DIG15: LED46.3 (V1), LED46.8 (V2), U2.3 (GRID15)
/sheet65E77961/DIG16: LED47.3 (V1), LED47.8 (V2), U2.4 (GRID16)
/sheet65E77961/DP: LED32.5 (DP), LED33.5 (DP), LED34.5 (DP), LED35.5 (DP), LED36.5 (DP), LED37.5 (DP), LED38.5 (DP), LED39.5 (DP), LED40.5 (DP), LED41.5 (DP), LED42.5 (DP), LED43.5 (DP), LED44.5 (DP), LED45.5 (DP), LED46.5 (DP), LED47.5 (DP), U2.17 (SEG8)
/sheet65E77961/E: LED32.1 (E), LED33.1 (E), LED34.1 (E), LED35.1 (E), LED36.1 (E), LED37.1 (E), LED38.1 (E), LED39.1 (E), LED40.1 (E), LED41.1 (E), LED42.1 (E), LED43.1 (E), LED44.1 (E), LED45.1 (E), LED46.1 (E), LED47.1 (E), U2.14 (SEG5)
/sheet65E77961/F: LED32.9 (F), LED33.9 (F), LED34.9 (F), LED35.9 (F), LED36.9 (F), LED37.9 (F), LED38.9 (F), LED39.9 (F), LED40.9 (F), LED41.9 (F), LED42.9 (F), LED43.9 (F), LED44.9 (F), LED45.9 (F), LED46.9 (F), LED47.9 (F), U2.15 (SEG6)
/sheet65E77961/G: LED32.10 (G), LED33.10 (G), LED34.10 (G), LED35.10 (G), LED36.10 (G), LED37.10 (G), LED38.10 (G), LED39.10 (G), LED40.10 (G), LED41.10 (G), LED42.10 (G), LED43.10 (G), LED44.10 (G), LED45.10 (G), LED46.10 (G), LED47.10 (G), U2.16 (SEG7)
GND: C2.2, C3.2, C4.2, C5.2, C6.2, C7.2, C8.2, C9.2, U1.5 (GND), U1.19 (GND), U1.28 (GND), U2.5 (GND), U2.19 (GND), U2.28 (GND), U3.5 (GND), U3.19 (GND), U3.28 (GND), U4.5 (GND), U4.19 (GND), U4.28 (GND), U5.5 (GND), U5.19 (GND), U5.28 (GND), U6.5 (GND), U6.19 (GND), U6.28 (GND), U7.5 (GND), U7.19 (GND), U7.28 (GND), U8.5 (GND), U8.19 (GND), U8.28 (GND); also elsewhere on the board

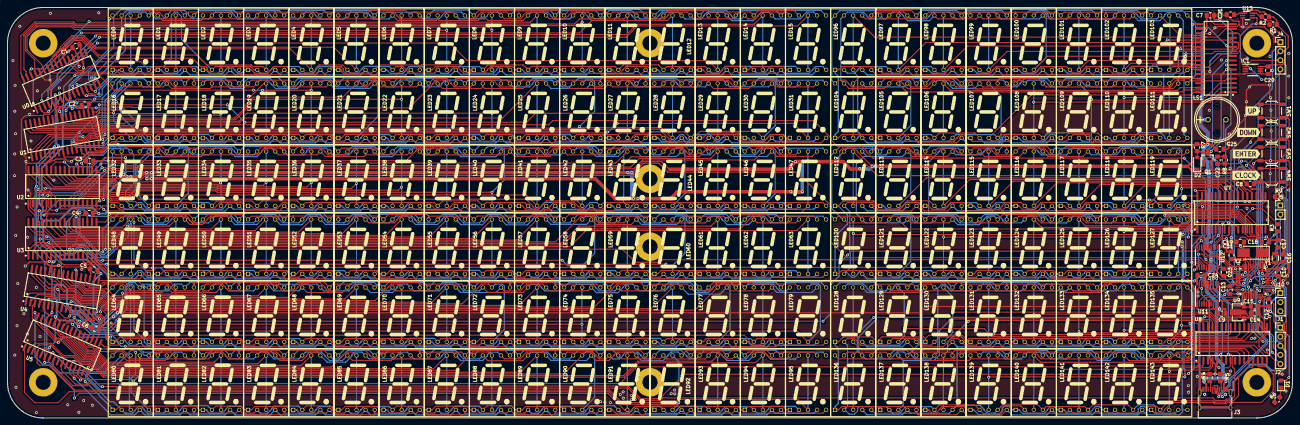
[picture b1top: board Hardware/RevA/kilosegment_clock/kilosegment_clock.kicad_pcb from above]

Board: 2 copper layers, 360.0 x 115.0 mm, 221 parts (1 on the bottom side), 268 nets.

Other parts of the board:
kibuzzard-6249F0CC, kibuzzard-6249F13F, kibuzzard-6249F15D, kibuzzard-6249F086: G***; label
